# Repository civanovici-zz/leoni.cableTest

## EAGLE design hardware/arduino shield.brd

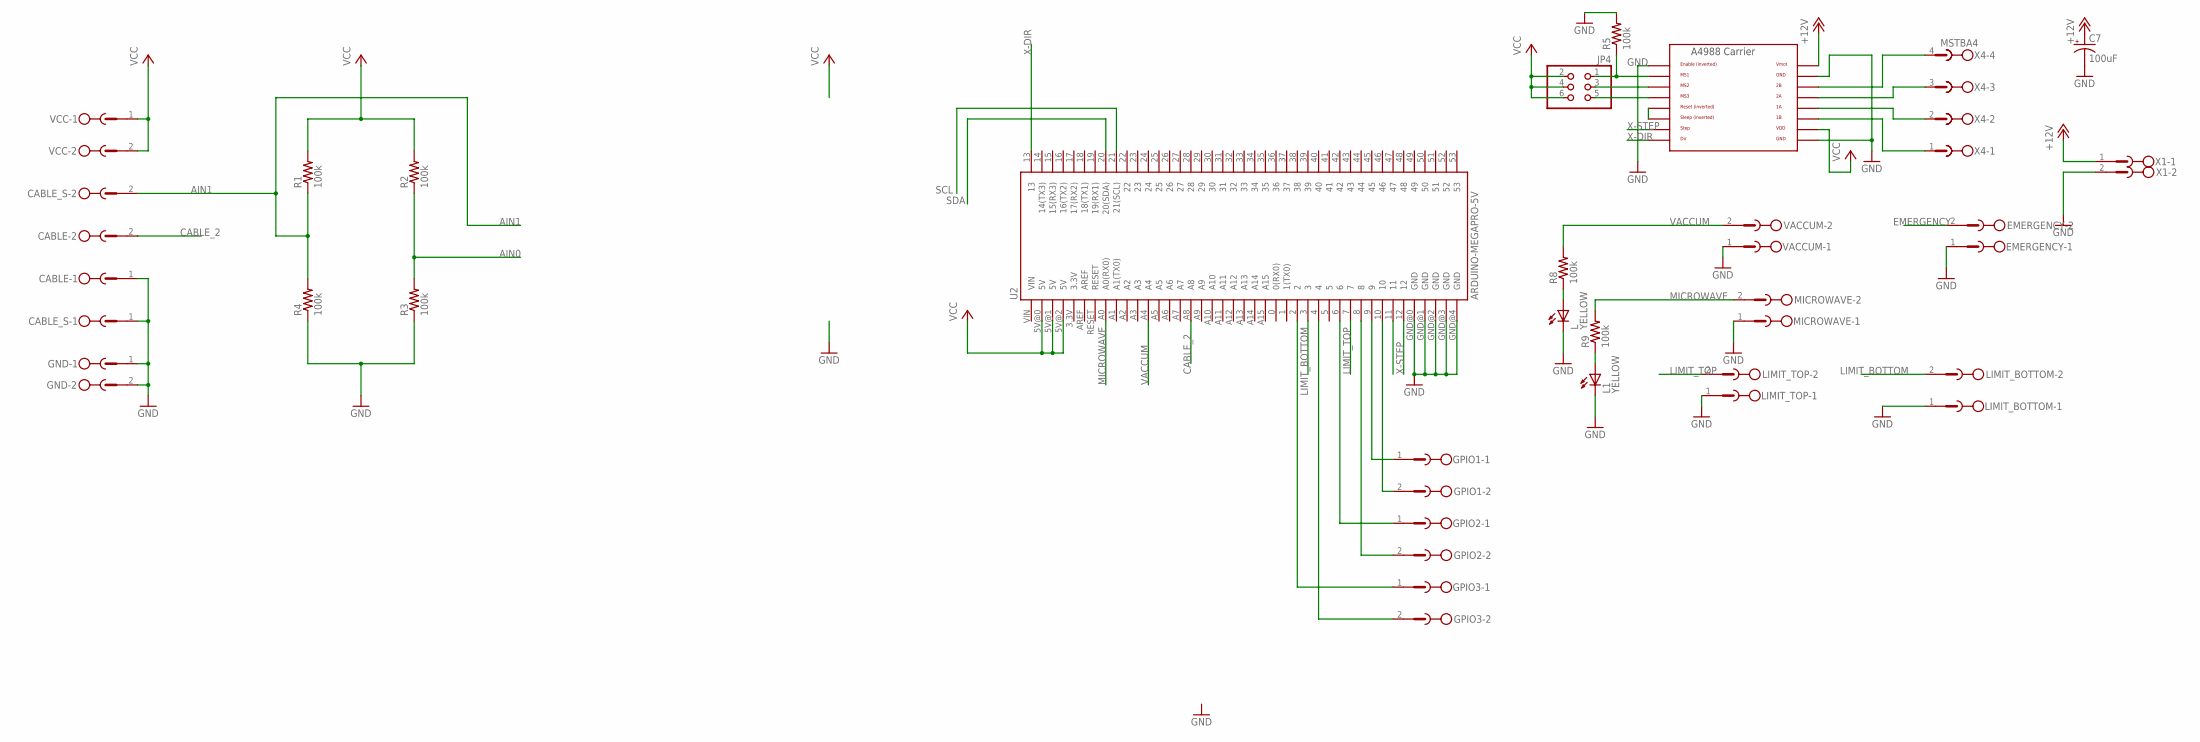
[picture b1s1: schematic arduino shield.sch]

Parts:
C7: 100uF; 153CLV-0605
CABLE: MSTBV2
CABLE_S: MSTBV2
EMERGENCY: MSTBV2
GND: MSTBV2
GPIO1, GPIO2, GPIO3: MSTBV2
JP4: PINHD-2X3; 2X03
L, L1: YELLOW; CHIP-LED0805
LIMIT_BOTTOM: MSTBV2
LIMIT_TOP: MSTBV2
MICROWAVE: MSTBV2
R1, R2, R3, R4, R5, R8, R9: 100k; R0805
U2: ARDUINO-MEGAPRO-5V; ARDUINO_MEGA-PRO-5V
U$6: A4988BREAKOUT
VACCUM: MSTBV2
VCC: MSTBV2
X1: MSTBV2
X4: MSTBA4

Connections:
+12V: C7.+, U$6.VMOT, X1.1
AIN0: R2.1, R3.2
AIN1: CABLE_S.2, R1.1, R4.2
CABLE_2: CABLE.2, U2.A8
EMERGENCY: EMERGENCY.2, U2.11
GND: C7.-, CABLE.1, CABLE_S.1, EMERGENCY.1, GND.1, GND.2, L.C, L1.C, LIMIT_BOTTOM.1, LIMIT_TOP.1, MICROWAVE.1, R3.1, R4.1, R5.2, U2.GND@0 (GND), U2.GND@1 (GND), U2.GND@2 (GND), U2.GND@3 (GND), U2.GND@4 (GND), U$6.EN, U$6.GND, U$6.GND@0 (GND), VACCUM.1, X1.2
LIMIT_BOTTOM: LIMIT_BOTTOM.2, U2.3
LIMIT_TOP: LIMIT_TOP.2, U2.7
MICROWAVE: MICROWAVE.2, R9.2, U2.A0 (A0(RX0))
unnamed: L.A, R8.1
unnamed: L1.A, R9.1
unnamed: GPIO1.2, U2.10
unnamed: GPIO1.1, U2.9
unnamed: GPIO2.2, U2.8
unnamed: GPIO2.1, U2.6
unnamed: GPIO3.2, U2.4
unnamed: GPIO3.1, U2.2
unnamed: JP4.1, R5.1, U$6.MS1
unnamed: JP4.3, U$6.MS2
unnamed: JP4.5, U$6.MS3
unnamed: U$6.RST, U$6.SLP (SLEEP)
unnamed: U$6.2B, X4.4
unnamed: U$6.2A, X4.3
unnamed: U$6.1A, X4.2
unnamed: U$6.1B, X4.1
SCL: U2.21 (21(SCL))
SDA: U2.20 (20(SDA))
VACCUM: R8.2, U2.A4, VACCUM.2
VCC: JP4.2, JP4.4, JP4.6, R1.2, R2.2, U2.5V@0 (5V), U2.5V@1 (5V), U2.5V@2 (5V), U$6.VDD, VCC.1, VCC.2
X-DIR: U2.13, U$6.DIR
X-STEP: U2.12, U$6.STEP

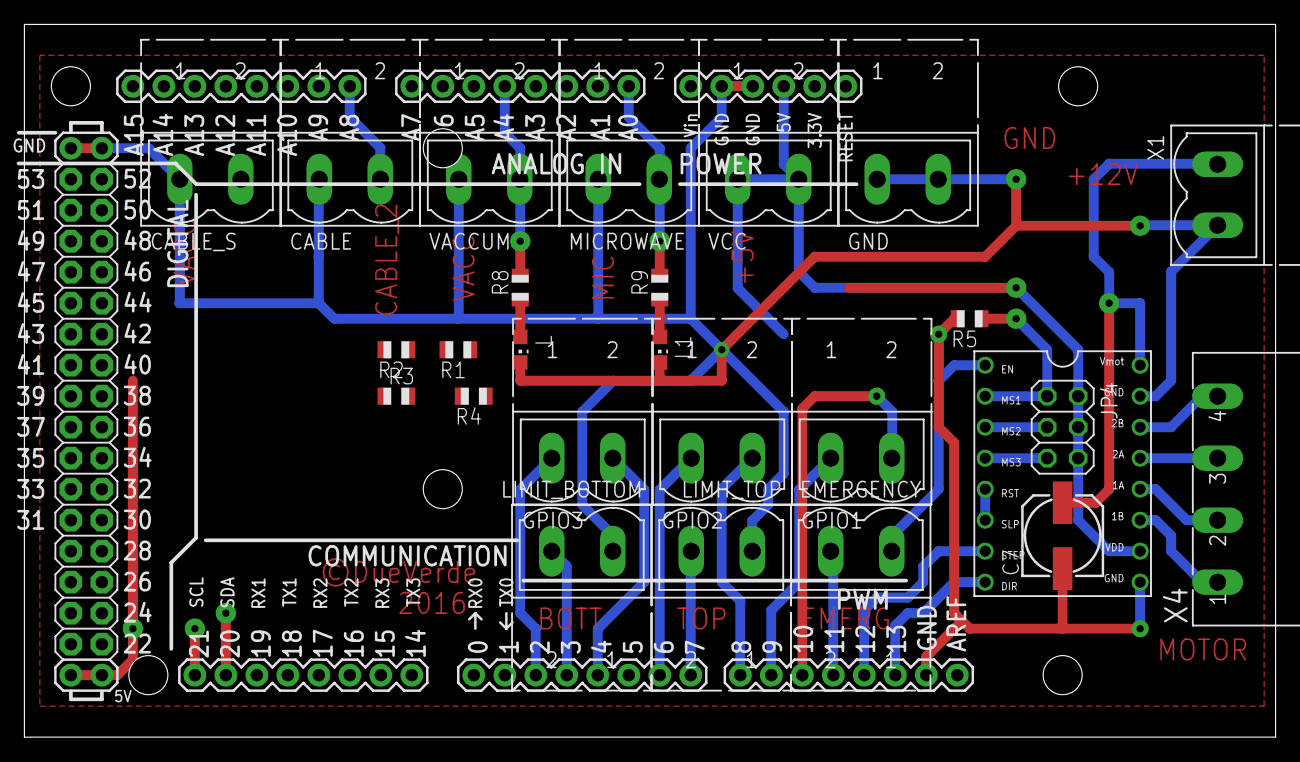
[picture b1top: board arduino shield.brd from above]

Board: 2 copper layers, 102.5 x 58.4 mm, 27 parts (0 on the bottom side), 29 nets.

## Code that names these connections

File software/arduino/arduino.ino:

#define MOTOR_STEP_PIN 9
#define MOTOR_DIR_PIN 10
#define VACCUM_PIN 6
#define MICROWAVE_PIN 5
#define LIMIT_TOP_PIN A3
#define LIMIT_BOTTOM_PIN A2
#define EMERGENCY_PIN A5
#define CABLE1_PIN A1
#define CABLE2_PIN A0
#define CABLES_PIN A4

#define COMMAND_MOTOR_STOP 48 //0
#define COMMAND_MOTOR_UP 49   //1
#define COMMAND_MOTOR_DOWN 50 //2
#define COMMAND_VACCUM_ON 51  //3
#define COMMAND_VACCUM_OFF 52 //4
#define COMMAND_MICROWAVE_ON 53//5
#define COMMAND_MICROWAVE_OFF 54//6
#define COMMAND_MEASURE_CURRENT 55//7
#define COMMAND_READ_CABLE_CONNECTION 56//8
#define COMMAND_GET_LIMIT_SWITCH_STATE 57//9
#define MOVING_UP 1
#define MOVING_DOWN 2
#define MOVING_NONE 0

boolean isMoving=false;
int moveDirection=0;

boolean emergencyState = false;
boolean bottomLimitState = false;
boolean topLimitState = false; 
boolean watchAttachedCable = false;

//debounce emergency
long debounceDelay = 50;    // the debounce time; increase if the output flickers
long lastDebounceTimeEmergency = 0;  // the last time the output pin was toggled
int lastEmergencyState=1;

long lastDebounceTimeTopLimit = 0 ;
int lastTopLimitState = 1;

long lastDebounceTimeBottomLimit = 0 ;
int lastBottomLimitState = 1;

int movingDirection =0;


void setup(){
  Serial.begin(9600);
  pinMode(MOTOR_STEP_PIN,OUTPUT);
  pinMode(MOTOR_DIR_PIN,OUTPUT);
  pinMode(VACCUM_PIN,OUTPUT);
  pinMode(MICROWAVE_PIN,OUTPUT);

  digitalWrite(MICROWAVE_PIN,LOW);
  digitalWrite(VACCUM_PIN,LOW);
    
  pinMode(LIMIT_TOP_PIN, INPUT_PULLUP);
  pinMode(LIMIT_BOTTOM_PIN, INPUT_PULLUP);
  pinMode(EMERGENCY_PIN, INPUT_PULLUP);
  pinMode(CABLE1_PIN, INPUT_PULLUP);
  pinMode(CABLE2_PIN, INPUT_PULLUP);
  pinMode(CABLES_PIN, INPUT_PULLUP);
  digitalWrite(MOTOR_DIR_PIN, HIGH);
}

void loop(){
  if(Serial.available()>0){
    int byte = Serial.read();
    String message ="OK";
    switch(byte){
      case COMMAND_MOTOR_STOP:
        isMoving = false;
        movingDirection =MOVING_NONE;
        break;
      case COMMAND_MOTOR_UP:
        digitalWrite(MOTOR_DIR_PIN, LOW);
        movingDirection = MOVING_UP;
        delay(100);
        isMoving = true;
        break;
      case COMMAND_MOTOR_DOWN:
        digitalWrite(MOTOR_DIR_PIN, HIGH);
        movingDirection = MOVING_DOWN;
        delay(100);
        isMoving = true;
        break;
      case COMMAND_VACCUM_ON:
        digitalWrite(VACCUM_PIN, HIGH);
        break;
      case COMMAND_VACCUM_OFF:
        digitalWrite(VACCUM_PIN, LOW);
        break;
      case COMMAND_MICROWAVE_ON:
        digitalWrite(MICROWAVE_PIN, HIGH);
        break;
      case COMMAND_MICROWAVE_OFF:
        digitalWrite(MICROWAVE_PIN, LOW);
        break;
      case COMMAND_MEASURE_CURRENT:
        measureLeakCurrent();
        break;
      case COMMAND_READ_CABLE_CONNECTION:
        measureCableConnection();
        break;
      case COMMAND_GET_LIMIT_SWITCH_STATE:
        sendEvent(String("LIMIT_SWITCH:")+String(topLimitState)+String(":")+String(bottomLimitState));
        break;
      default:
        message = "UNKNOW COMMAND";
        Serial.print(byte);
        break;     
    }
    Serial.print(byte);
  Serial.println(message);
  Serial.flush();  
  }
  readMachineState();
  driveStepper();
}


void readMachineState(){

  int topLimit,bottomLimit,emergency;
  
  bottomLimit = digitalRead(LIMIT_BOTTOM_PIN);
  topLimit = digitalRead(LIMIT_TOP_PIN);
  emergency = digitalRead(EMERGENCY_PIN);
  debounceEmergency(emergency);
  debounceTopLimit(topLimit);
  debounceBottomLimit(bottomLimit);
}

void measureCableConnection(){
  int cableConnection = analogRead(CABLE2_PIN);
  sendEvent(String("CABLE_CONNECTION:")+String(cableConnection));
}

void measureLeakCurrent(){
  int cableConnection = analogRead(CABLE2_PIN);
  int leakCurrent = analogRead(CABLE1_PIN);
  sendEvent(String("LEAK_CURRENT:")+String(leakCurrent)+String(":")+String(cableConnection));
}


void sendEvent(String msg){
  Serial.println("EVENT:"+msg);
}

//drive stepper motor
void driveStepper(){
  if(isMoving==false)
    return;   
  if(movingDirection ==MOVING_UP && topLimitState == 0)
  {
    movingDirection = MOVING_NONE;
    isMoving =false;
  }

  if(movingDirection ==MOVING_DOWN && bottomLimitState == 0)
  {
    movingDirection = MOVING_NONE;
    isMoving =false;
  }
  
  int speedDelay=500;
  digitalWrite(MOTOR_STEP_PIN, LOW);
  delayMicroseconds(4);
  digitalWrite(MOTOR_STEP_PIN, HIGH);
  delayMicroseconds(speedDelay);

}

void debounceEmergency(int reading){
  if(reading != lastEmergencyState){
    lastDebounceTimeEmergency =millis();
  } 
  if((millis() - lastDebounceTimeEmergency) > debounceDelay) {
    if(reading != emergencyState){
    emergencyState = reading;
      sendEvent(String("EMERGENCY:")+String(emergencyState));
      isMoving = false;     
      movingDirection = MOVING_NONE; 
    }
  }
  lastEmergencyState = reading;
}

void debounceTopLimit(int reading){
  if(reading != lastTopLimitState){
    lastDebounceTimeTopLimit =millis();
  } 
  if((millis() - lastDebounceTimeTopLimit) > debounceDelay) {
    if(reading != topLimitState){
      topLimitState = reading;
      if(movingDirection == MOVING_UP){
        sendEvent(String("TOP_LIMIT:")+String(topLimitState));
        isMoving = false;  
        movingDirection = MOVING_NONE;   
      }
    }
  }
  lastTopLimitState = reading;
}

void debounceBottomLimit(int reading){
  if(reading != lastBottomLimitState){
    lastDebounceTimeBottomLimit =millis();
  } 
  if((millis() - lastDebounceTimeBottomLimit) > debounceDelay) {
    if(reading != bottomLimitState){
      bottomLimitState = reading;
      if(movingDirection == MOVING_DOWN){
        sendEvent(String("BOTTOM_LIMIT:")+String(bottomLimitState));
        isMoving = false;   
        movingDirection = MOVING_NONE;   
      }
    }
  }
  lastBottomLimitState = reading;
}

void debounceInput(int reading, int lastInputState, long lastDebounceTime, int inputState,String eventName){
  if(reading != lastInputState){
    lastDebounceTime =millis();
  }  
  if((millis() - lastDebounceTime) > debounceDelay) {
    if(reading != inputState){
      inputState = reading;
      sendEvent(String(eventName)+String(inputState));
      isMoving = false;     
    }
  }
  lastInputState = reading;
}

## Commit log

2015-12-06 :confetti_ball: Added .gitattributes & .gitignore files
2015-12-06 Revert ":confetti_ball: Added .gitattributes & .gitignore files"
    This reverts commit 628f0cbed474e2e23a358f8e716c736c2299bb77.
2016-02-03 remove unsued files
2016-02-03 adding initial node app
2016-02-03 change default folder
2016-02-03 updated node dependencies
2016-02-03 added ignore file
2016-02-13 application skeleton
2016-02-13 default html
2016-02-15 arduino files added
2016-02-15 some changes
2016-02-15 update app-server
2016-02-21 other updates
2016-02-21 electron files
2016-02-21 update for electron
2016-02-21 electron file update
2016-02-22 update on state machine logic
2016-02-22 algorithm updates
2016-02-23 current measurement
2016-02-24 finish detection algorithm
2016-02-24 remove bundle.js
2016-02-25 new board
2016-02-29 small udate from rapsberry
2016-02-29 hardware changes
2016-02-29 ui updates
2016-03-01 added printer, barcode
2016-03-04 arduino update

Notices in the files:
hardware/arduino shield.brd:
©DueVerde
parts and their libraries:
sparkfun: Licensing: Creative Commons ShareAlike 4.0 International - https://creativecommons.org/licenses/by-sa/4.0
